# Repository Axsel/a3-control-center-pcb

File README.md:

# A3 Control Center PCB

Revision A design for a USB-powered ESP32-WROOM-32E-N4 controller with independent
high-speed and fault-tolerant CAN buses, a replaceable SSD1306 OLED, and an
analog composite-video output.

## Status

Phase 1 architecture was approved on 2026-10-02. The Phase 2 schematic and
100 x 70 mm four-layer PCB are electrically complete for USB/power, ESP32/UI,
CAN_HS, CAN_FT, and composite video. A deterministic 19-stage layout rebuild
under KiCad 10.0.6 now reports **ERC 0, DRC 0, and 0 unconnected items**. A local
pre-release manufacturing audit package exists under
`manufacturing/generated/rev-a-audit/`, but no order-ready manufacturing release
has been created. LCSC identities are qualified for all 97 candidate
references; high-voltage C1 now uses PSA FV32N472J102EFG / C5156737 from JLC
global sourcing. The U5, U10, J1, and J60 critical footprints have passed
independent dimensional audits; JLC confirmation of the RCA plated slot, USB
connector assembly handling, physical connector fit checks, stock reservation,
and purchasing/source resolution remain release gates. The three-button part
identity is resolved by an audited same-footprint change to
TL3301NF260QG/C273528; the current consolidated JLC workbook allocates all six
needed switches. The former CP2102N stock gate is closed by using
Silicon Labs' electrically identical tape-and-reel order code
CP2102N-A02-GQFN28R/C964632. The project owner has
accepted deferring composite-video electrical and JVC compatibility validation
until assembled Revision A boards arrive; those tests remain mandatory during
bring-up but are no longer a prototype-order blocker.
The manufacturing contract requires JLCPCB to fit every board connector:
J1/J10/J20/J40/J60 are present in both the candidate BOM and full CPL for
manual/wave assembly; the user is not expected to solder connectors.
An independent layer-by-layer Gerber/drill render review is also complete, with
its evidence and limitations recorded in `docs/rev-a-fabrication-review.md`.

For quick repository browsing, see the
[Revision A rendered views](docs/revision-a-rendered-views.md), including the
complete schematic PDF, per-sheet previews, PCB top/bottom renders, assembly
drawing, and fabrication-layer images.

The originally requested ESP32-WROOM-32 was replaced with the manufacturer-
recommended `ESP32-WROOM-32E-N4` after project-owner authorization. The change
preserves the classic ESP32 architecture, 4 MB flash, PCB antenna, DAC1/DAC2,
TWAI, firmware pin map, and module envelope while avoiding an NRND part. The
manufacturer land pattern and antenna keepout for the 32E are mandatory.

## Repository map

- `docs/`: architecture, interfaces, calculations, decisions, and test plans
- `hardware/`: KiCad 10 project, design rules, and project-local libraries
- `datasheets/`: source index; vendor PDFs are not copied into Git by default
- `bom/`: controlled, provisional BOM
- `firmware/`: synchronized GPIO contract and video feasibility notes
- `scripts/`: KiCad CLI wrapper plus validation/export automation
- `manufacturing/`: controlled release area plus the tracked Revision A audit
  snapshot used by the rendered-view index

The remaining JLC engineering and global-sourcing questions are consolidated
in `manufacturing/jlcpcb-support-request.md` for submission before payment.

## Tooling note

The container now has KiCad 10.0.6 and its matching official symbols,
footprints, templates, and 3D models. Use `./scripts/kicad-cli`; headless ERC and
DRC were validated against an installed reference project. Installation details
and the remaining Phase 2 inputs are recorded in `docs/toolchain.md`.

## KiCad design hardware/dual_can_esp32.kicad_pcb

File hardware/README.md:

# Hardware workspace

Phase 2 contains a native KiCad 10.0.6 project, a complete hierarchical
schematic, a four-layer 100 x 70 mm PCB with all 130 electrical footprints plus
four board-only M3 mounting holes functionally placed, JLCPCB-oriented custom
design rules, and project-local library tables. USB data, both converter local
power stages, protected USB 5 V and 5V_FT distribution, and the MCP2515 crystal
nets are routed over a filled continuous L2 ground plane. The rest of the board
is intentionally still in routing development; this is not a manufacturing
release.

Project-local symbol and footprint libraries contain the Kycon KLPX RCA and
TPS63070 RNM0015A land patterns. The DFR0486 OLED is cable mounted through an
official-library JST-PH footprint; any device whose installed-library
pin/package mapping cannot be proven from its datasheet remains a local-library
candidate. The KiCad 10 official USB4105 footprint is present and matches the
selected GCT family. Its signal/contact orientation and edge-mounted
shell-stake clearances have been checked in the current placement; a final
drawing/Gerber overlay is still required before release.

The MCU is `ESP32-WROOM-32E-N4`. Its KiCad footprint has been checked for the 38
castellated pads, thermal ground land/vias, module outline, and antenna keepout
against Figure 13 of Espressif datasheet v2.1. The antenna is placed at the top
board edge; the keepout must be rechecked in final Gerbers after zones exist.

J20/J40 use Phoenix Contact item 1715734 (`MKDS 1,5/ 3-5,08`) and the audited
KiCad 10 official 5.08 mm MKDS footprint. This is the three-independent-potential
part; the similarly named internally commoned `-B-` variant is not acceptable.

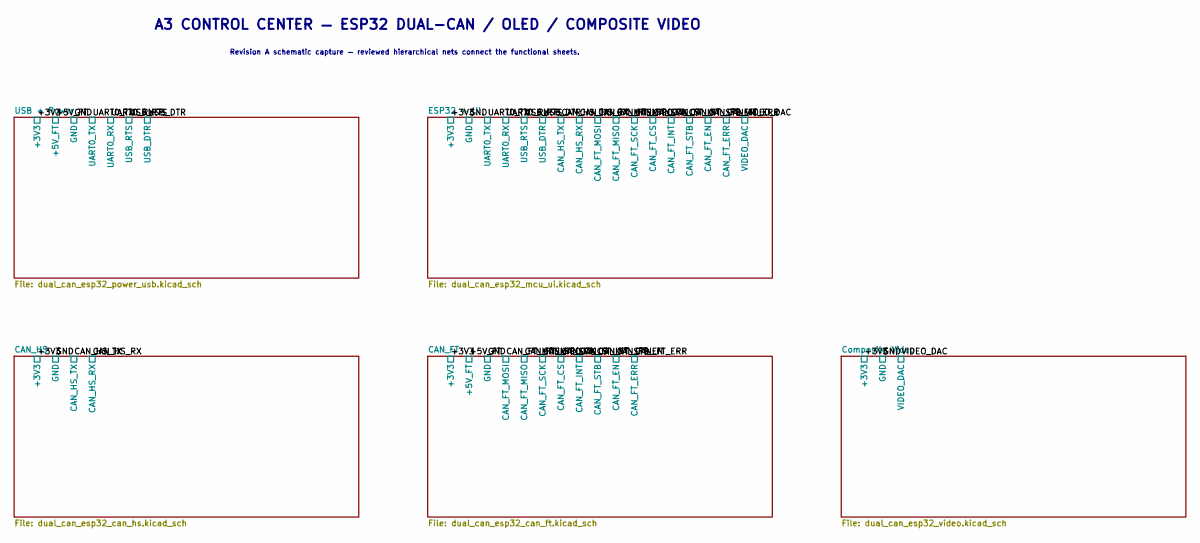
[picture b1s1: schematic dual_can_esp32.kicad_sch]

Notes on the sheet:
Revision A schematic capture — reviewed hierarchical nets connect the functional sheets.
A3 CONTROL CENTER — ESP32 DUAL-CAN / OLED / COMPOSITE VIDEO

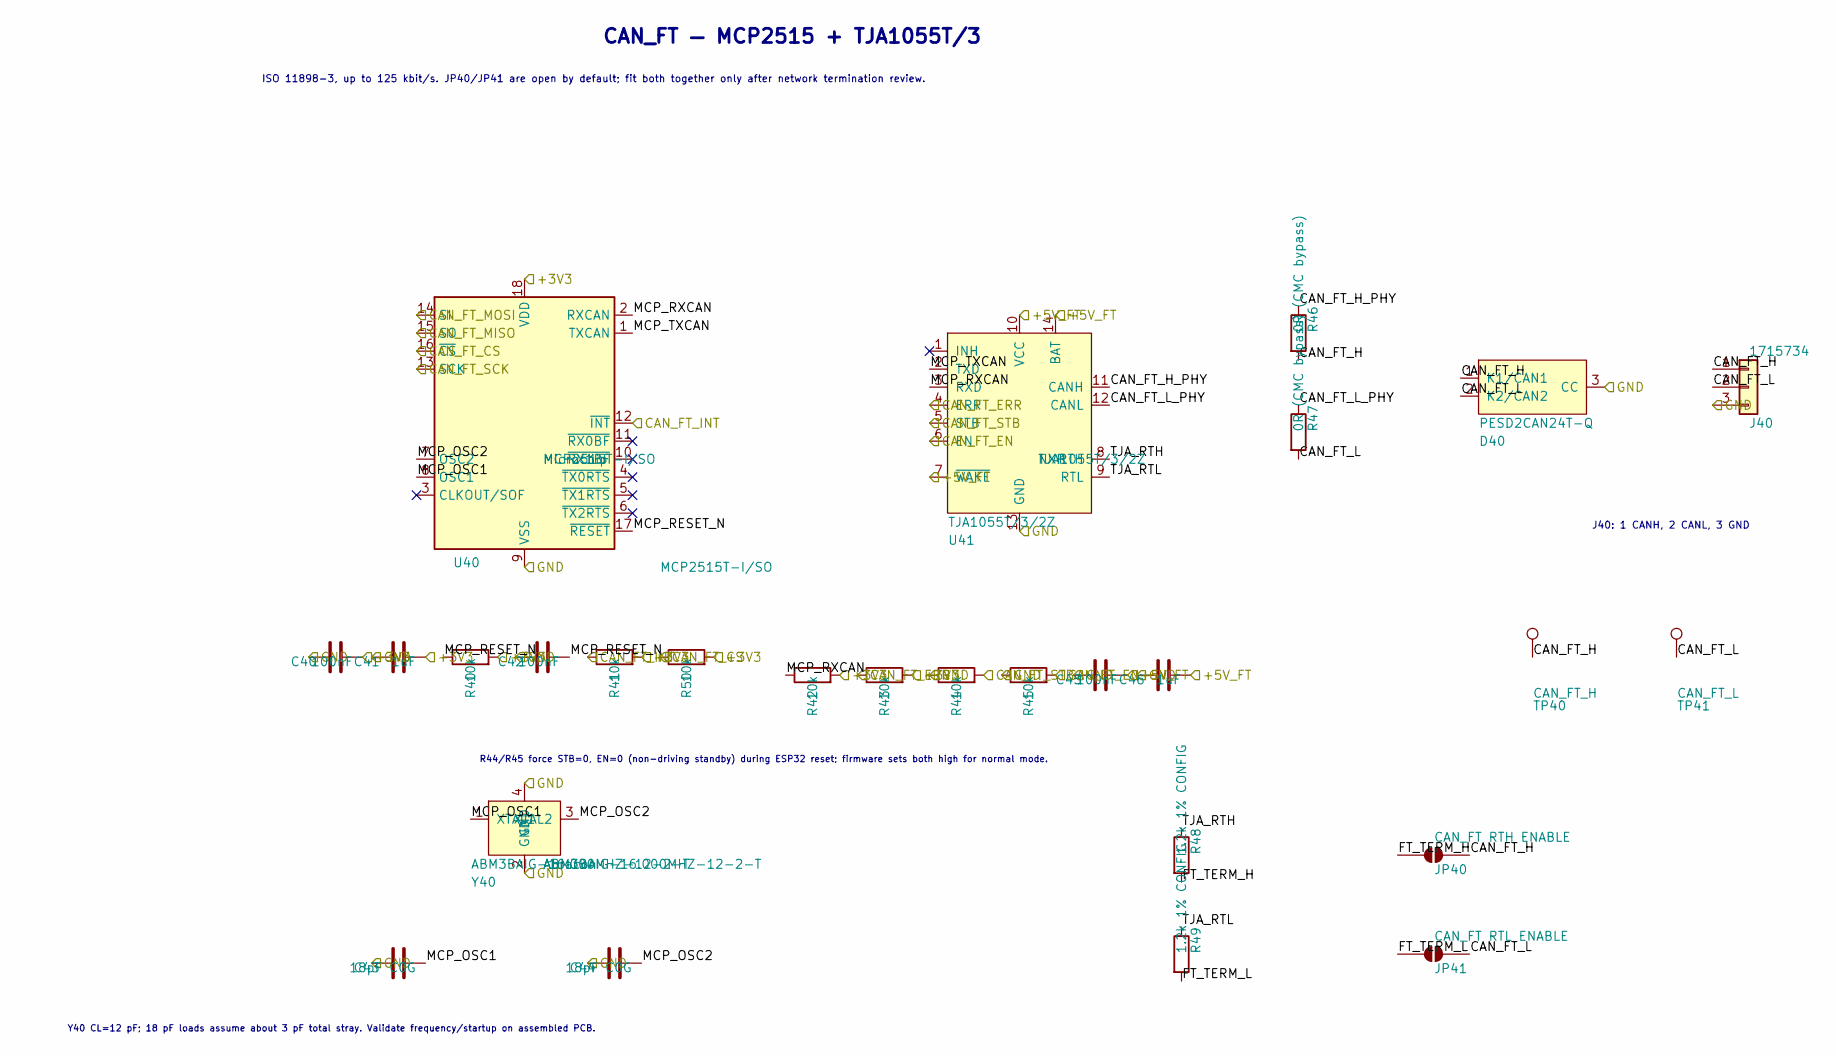
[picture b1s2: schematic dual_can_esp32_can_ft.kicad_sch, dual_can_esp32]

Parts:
C40, C42, C45: 100nF; C_0603_1608Metric
C41, C46: 1uF; C_0805_2012Metric
C43, C44: 18pF C0G; C_0603_1608Metric
D40: PESD2CAN24T-Q; SOT-23
J40: 1715734; TerminalBlock_Phoenix_MKDS-1,5-3-5.08_1x03_P5.08mm_Horizont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
JP40: CAN_FT RTH ENABLE; SolderJumper-2_P1.3mm_Open_RoundedPad1.0x1.5mm
JP41: CAN_FT RTL ENABLE; SolderJumper-2_P1.3mm_Open_RoundedPad1.0x1.5mm
R40, R41, R42, R43, R44, R45, R50: 10k; R_0603_1608Metric
R46, R47: 0R (CMC bypass); R_0603_1608Metric
R48, R49: 1.2k 1% CONFIG; R_0603_1608Metric
TP40: CAN_FT_H; TestPoint_Pad_D1.0mm
TP41: CAN_FT_L; TestPoint_Pad_D1.0mm
U40: MCP2515T-I/SO; SOIC-18W_7.5x11.6mm_P1.27mm; MPN MCP2515T-I/SO
U41: TJA1055T/3/2Z; SO-14_3.9x8.65mm_P1.27mm; MPN TJA1055T/3/2Z
Y40: ABM3BAIG-16.000MHZ-12-2-T; Crystal_SMD_5032-4Pin_5.0x3.2mm; MPN ABM3BAIG-16.000MHZ-12-2-T

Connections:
/+3V3: C40.2, C41.2, R40.2, R41.2, R42.2, R43.2, R50.2, U40.18 (VDD); also elsewhere on the board
/+5V_FT: C45.2, C46.2, U41.7 (~WAKE), U41.10 (VCC), U41.14 (BAT); also elsewhere on the board
/CAN_FT/CAN_FT_H: D40.1 (K1/CAN1), J40.1, JP40.2 (B), R46.2, TP40.1 (1_1)
/CAN_FT/CAN_FT_H_PHY: R46.1, U41.11 (CANH)
/CAN_FT/CAN_FT_L: D40.2 (K2/CAN2), J40.2, JP41.2 (B), R47.2, TP41.1 (1_1)
/CAN_FT/CAN_FT_L_PHY: R47.1, U41.12 (CANL)
/CAN_FT/FT_TERM_H: JP40.1 (A), R48.2
/CAN_FT/FT_TERM_L: JP41.1 (A), R49.2
/CAN_FT/MCP_OSC1: C43.2, U40.8 (OSC1), Y40.1 (XTAL1)
/CAN_FT/MCP_OSC2: C44.2, U40.7 (OSC2), Y40.3 (XTAL2)
/CAN_FT/MCP_RESET_N: C42.2, R40.1, U40.17 (~RESET)
/CAN_FT/MCP_RXCAN: R42.1, U40.2 (RXCAN), U41.3 (RXD)
/CAN_FT/MCP_TXCAN: U40.1 (TXCAN), U41.2 (TXD)
/CAN_FT/TJA_RTH: R48.1, U41.8 (RTH)
/CAN_FT/TJA_RTL: R49.1, U41.9 (RTL)
/CAN_FT_CS: R50.1, U40.16 (~CS); also elsewhere on the board
/CAN_FT_EN: R45.2, U41.6 (EN); also elsewhere on the board
/CAN_FT_ERR: R43.1, U41.4 (ERR); also elsewhere on the board
/CAN_FT_INT: R41.1, U40.12 (~INT); also elsewhere on the board
/CAN_FT_MISO: U40.15 (SO); also elsewhere on the board
/CAN_FT_MOSI: U40.14 (SI); also elsewhere on the board
/CAN_FT_SCK: U40.13 (SCK); also elsewhere on the board
/CAN_FT_STB: R44.2, U41.5 (STB); also elsewhere on the board
/GND: C40.1, C41.1, C42.1, C43.1, C44.1, C45.1, C46.1, D40.3 (CC), J40.3, R44.1, R45.1, U40.9 (VSS), U41.13 (GND), Y40.2 (GND), Y40.4 (GND); also elsewhere on the board

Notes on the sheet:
R44/R45 force STB=0, EN=0 (non-driving standby) during ESP32 reset; firmware sets both high for normal mode.
J40: 1 CANH, 2 CANL, 3 GND
Y40 CL=12 pF; 18 pF loads assume about 3 pF total stray. Validate frequency/startup on assembled PCB.
CAN_FT — MCP2515 + TJA1055T/3
ISO 11898-3, up to 125 kbit/s. JP40/JP41 are open by default; fit both together only after network termination review.

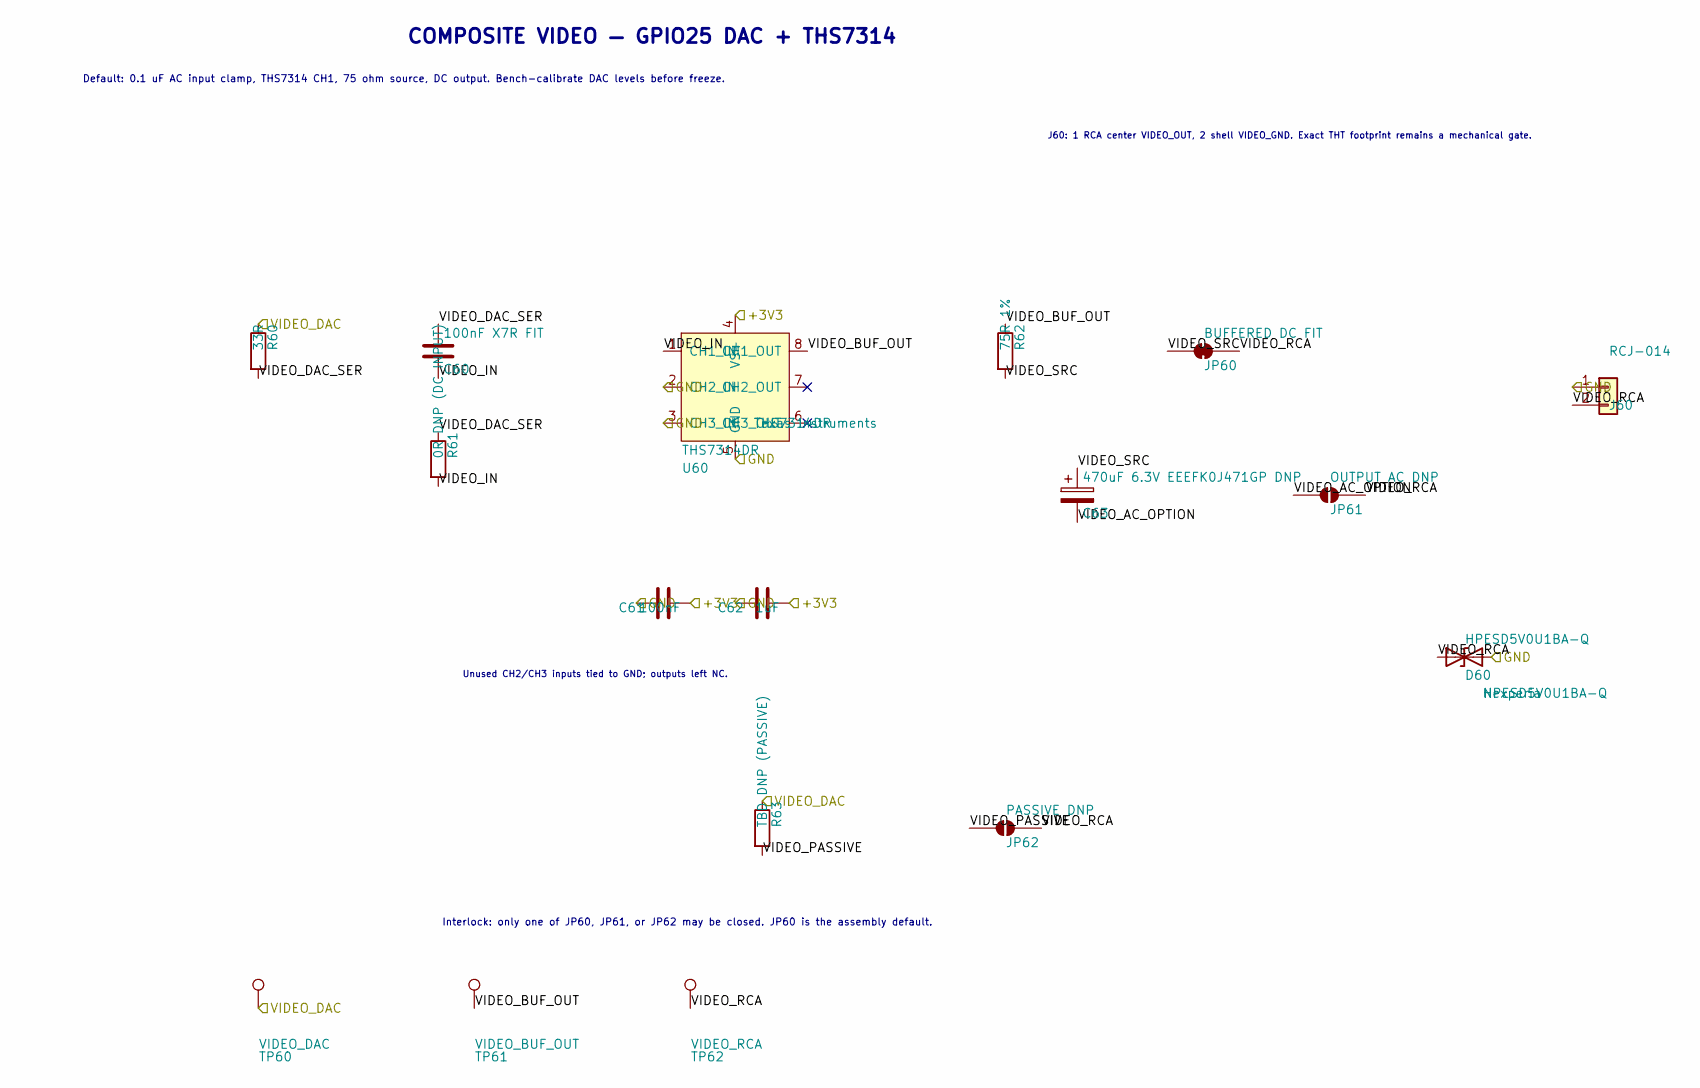
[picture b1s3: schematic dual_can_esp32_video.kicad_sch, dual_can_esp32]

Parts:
C60: 100nF X7R FIT; C_0805_2012Metric
C61: 100nF; C_0603_1608Metric
C62: 1uF; C_0805_2012Metric
C63: 470uF 6.3V EEEFK0J471GP DNP; CP_Elec_8x10
D60: HPESD5V0U1BA-Q; D_SOD-323; MPN HPESD5V0U1BA-Q
J60: RCJ-014
JP60: BUFFERED DC FIT; SolderJumper-2_P1.3mm_Bridged_RoundedPad1.0x1.5mm
JP61: OUTPUT AC DNP; SolderJumper-2_P1.3mm_Open_RoundedPad1.0x1.5mm
JP62: PASSIVE DNP; SolderJumper-2_P1.3mm_Open_RoundedPad1.0x1.5mm
R60: 33R; R_0603_1608Metric
R61: 0R DNP (DC INPUT); R_0603_1608Metric
R62: 75R 1%; R_0603_1608Metric
R63: TBD DNP (PASSIVE); R_0603_1608Metric
TP60: VIDEO_DAC; TestPoint_Pad_D1.0mm
TP61: VIDEO_BUF_OUT; TestPoint_Pad_D1.0mm
TP62: VIDEO_RCA; TestPoint_Pad_D1.0mm
U60: THS7314DR; SOIC-8_3.9x4.9mm_P1.27mm; MPN THS7314DR

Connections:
/+3V3: C61.2, C62.2, U60.4 (VS+); also elsewhere on the board
/Composite Video/VIDEO_AC_OPTION: C63.2, JP61.1 (A)
/Composite Video/VIDEO_BUF_OUT: R62.1, TP61.1 (1_1), U60.8 (CH1_OUT)
/Composite Video/VIDEO_DAC_SER: C60.1, R60.2, R61.1
/Composite Video/VIDEO_IN: C60.2, R61.2, U60.1 (CH1_IN)
/Composite Video/VIDEO_PASSIVE: JP62.1 (A), R63.2
/Composite Video/VIDEO_RCA: D60.1 (A1), J60.2, JP60.2 (B), JP61.2 (B), JP62.2 (B), TP62.1 (1_1)
/Composite Video/VIDEO_SRC: C63.1, JP60.1 (A), R62.2
/GND: C61.1, C62.1, D60.2 (A2), J60.1, U60.2 (CH2_IN), U60.3 (CH3_IN), U60.5 (GND); also elsewhere on the board
/VIDEO_DAC: R60.1, R63.1, TP60.1 (1_1); also elsewhere on the board

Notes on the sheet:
Default: 0.1 uF AC input clamp, THS7314 CH1, 75 ohm source, DC output. Bench-calibrate DAC levels before freeze.
J60: 1 RCA center VIDEO_OUT, 2 shell VIDEO_GND. Exact THT footprint remains a mechanical gate.
Interlock: only one of JP60, JP61, or JP62 may be closed. JP60 is the assembly default.
Unused CH2/CH3 inputs tied to GND; outputs left NC.
COMPOSITE VIDEO — GPIO25 DAC + THS7314

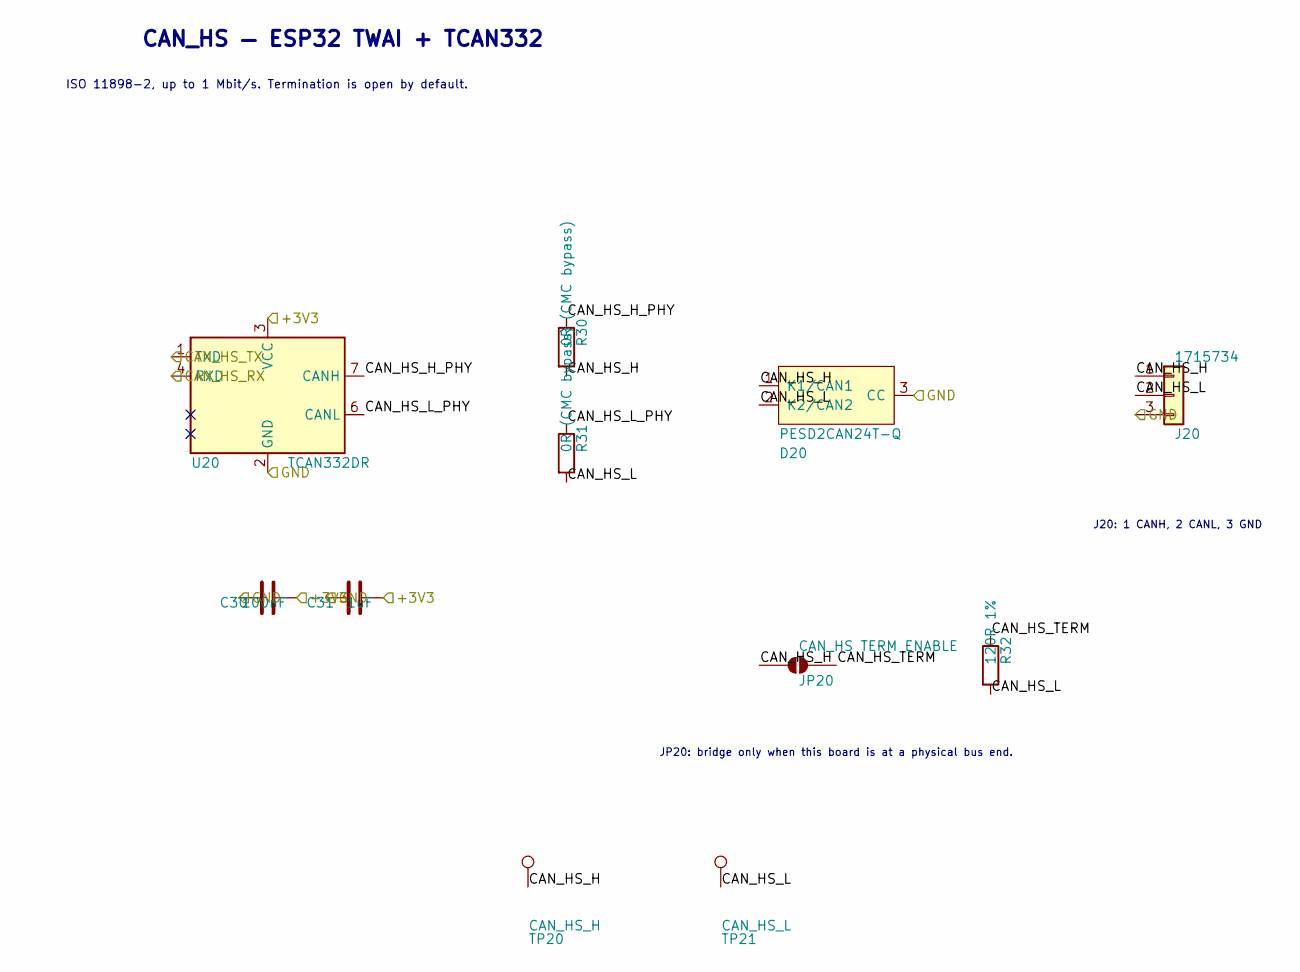
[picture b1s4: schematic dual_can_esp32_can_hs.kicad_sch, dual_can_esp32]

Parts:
C30: 100nF; C_0603_1608Metric
C31: 1uF; C_0805_2012Metric
D20: PESD2CAN24T-Q; SOT-23
J20: 1715734; TerminalBlock_Phoenix_MKDS-1,5-3-5.08_1x03_P5.08mm_Horizont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
JP20: CAN_HS TERM ENABLE; SolderJumper-2_P1.3mm_Open_RoundedPad1.0x1.5mm
R30, R31: 0R (CMC bypass); R_0603_1608Metric
R32: 120R 1%; R_0603_1608Metric
TP20: CAN_HS_H; TestPoint_Pad_D1.0mm
TP21: CAN_HS_L; TestPoint_Pad_D1.0mm
U20: TCAN332DR; SOIC-8_3.9x4.9mm_P1.27mm

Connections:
/+3V3: C30.2, C31.2, U20.3 (VCC); also elsewhere on the board
/CAN_HS/CAN_HS_H: D20.1 (K1/CAN1), J20.1, JP20.1 (A), R30.2, TP20.1 (1_1)
/CAN_HS/CAN_HS_H_PHY: R30.1, U20.7 (CANH)
/CAN_HS/CAN_HS_L: D20.2 (K2/CAN2), J20.2, R31.2, R32.2, TP21.1 (1_1)
/CAN_HS/CAN_HS_L_PHY: R31.1, U20.6 (CANL)
/CAN_HS/CAN_HS_TERM: JP20.2 (B), R32.1
/CAN_HS_RX: U20.4 (RXD); also elsewhere on the board
/CAN_HS_TX: U20.1 (TXD); also elsewhere on the board
/GND: C30.1, C31.1, D20.3 (CC), J20.3, U20.2 (GND); also elsewhere on the board

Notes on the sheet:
CAN_HS — ESP32 TWAI + TCAN332
J20: 1 CANH, 2 CANL, 3 GND
ISO 11898-2, up to 1 Mbit/s. Termination is open by default.
JP20: bridge only when this board is at a physical bus end.

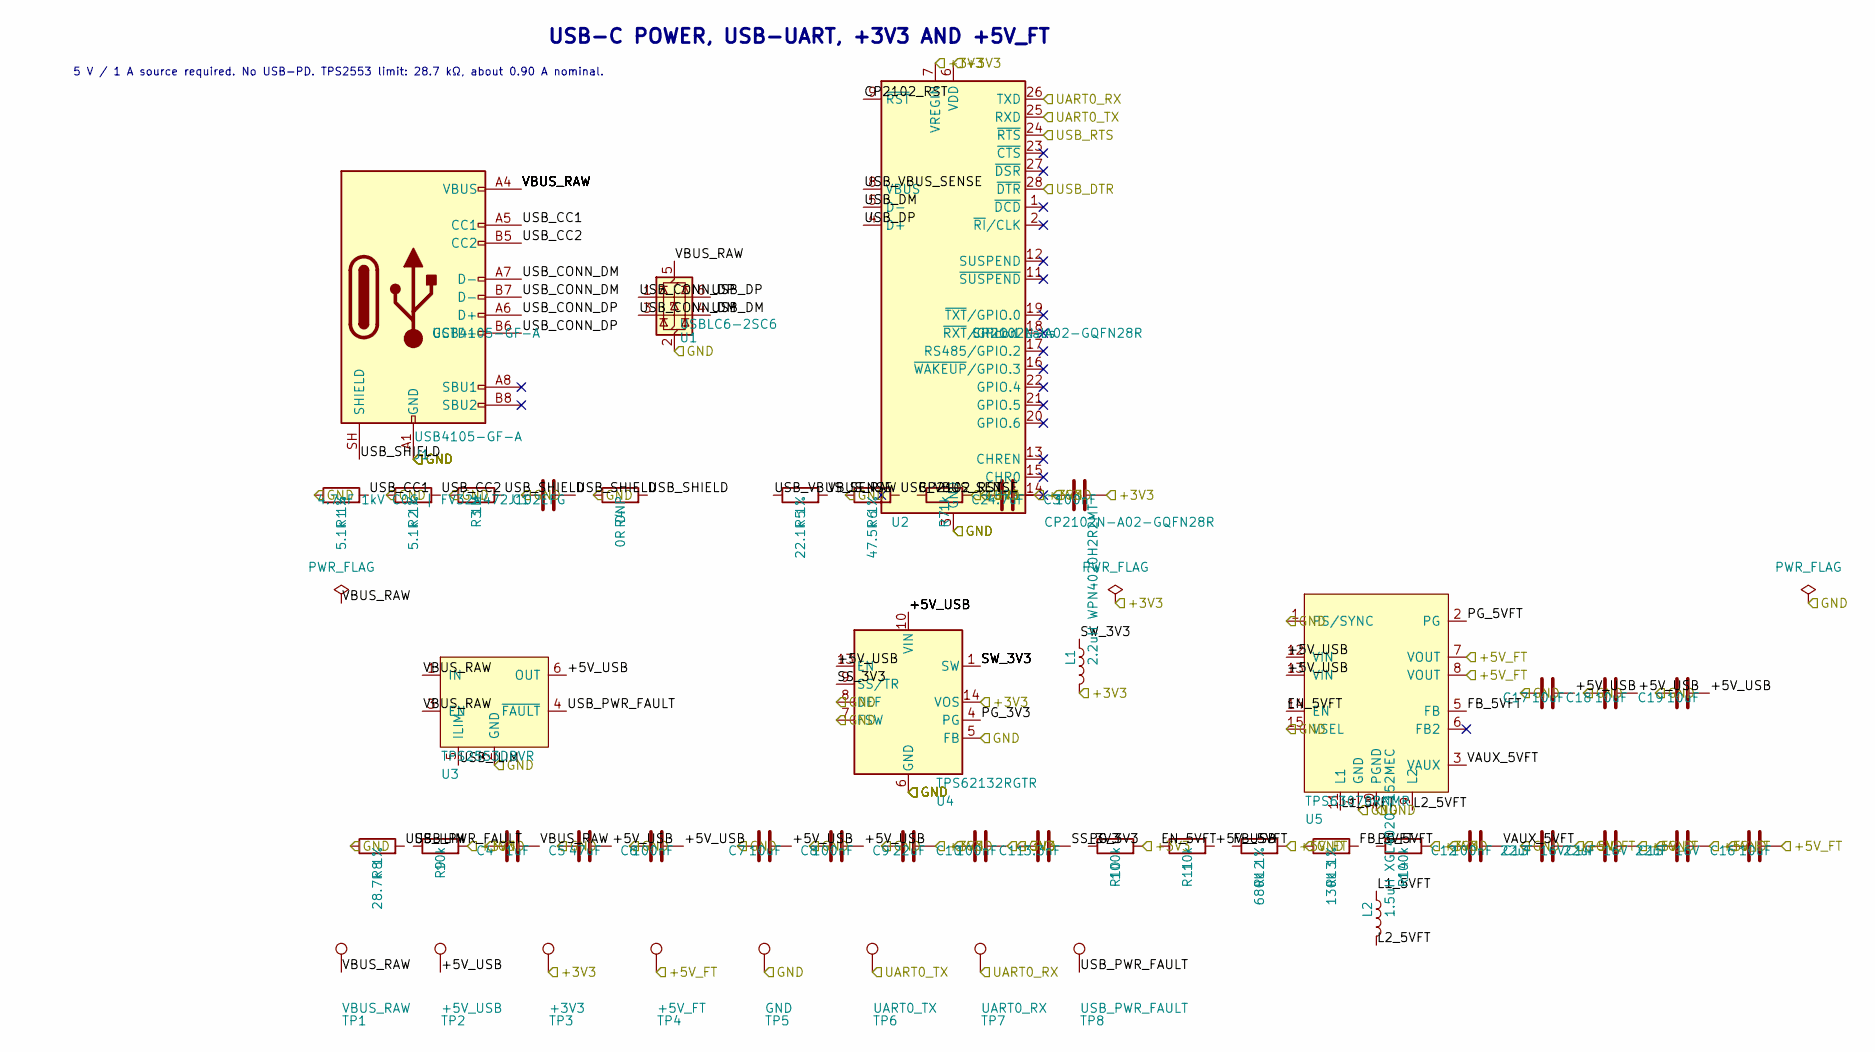
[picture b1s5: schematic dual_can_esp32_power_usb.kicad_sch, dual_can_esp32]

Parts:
C1: 4.7nF 1kV C0G | FV32N472J102EFG; C_1210_3225Metric
C2: 4.7uF; C_0805_2012Metric
C3, C6, C8, C10, C12: 100nF; C_0603_1608Metric
C4: 1uF; C_0805_2012Metric
C5: 47uF; C_1210_3225Metric
C7, C17, C18: 10uF; C_0805_2012Metric
C9: 22uF; C_0805_2012Metric
C11: 3.3nF; C_0603_1608Metric
C13, C14, C15: 22uF 16V; C_0805_2012Metric
C16, C19: 10uF; C_0603_1608Metric
J1: USB4105-GF-A; USB_C_Receptacle_GCT_USB4105-xx-A_16P_TopMnt_Horizontal; MPN USB4105-GF-A
L1: 2.2uH WPN4020H2R2MT; WPN4020H
L2: 1.5uH XGL4020-152MEC; L_Coilcraft_XxL4020
R1, R2: 5.1k 1%; R_0603_1608Metric
R3: 1M; R_0603_1608Metric
R4: 0R DNP; R_0603_1608Metric
R5: 22.1k 1%; R_0603_1608Metric
R6: 47.5k 1%; R_0603_1608Metric
R7: 1k; R_0603_1608Metric
R8: 28.7k 1%; R_0603_1608Metric
R9, R11: 10k; R_0603_1608Metric
R10, R14: 100k; R_0603_1608Metric
R12: 680k 1%; R_0603_1608Metric
R13: 130k 1%; R_0603_1608Metric
TP1: VBUS_RAW; TestPoint_Pad_D1.0mm
TP2: +5V_USB; TestPoint_Pad_D1.0mm
TP3: +3V3; TestPoint_Pad_D1.0mm
TP4: +5V_FT; TestPoint_Pad_D1.0mm
TP5: GND; TestPoint_Pad_D1.0mm
TP6: UART0_TX; TestPoint_Pad_D1.0mm
TP7: UART0_RX; TestPoint_Pad_D1.0mm
TP8: USB_PWR_FAULT; TestPoint_Pad_D1.0mm
U1: USBLC6-2SC6; SOT-23-6
U2: CP2102N-A02-GQFN28R; QFN-28-1EP_5x5mm_P0.5mm_EP3.35x3.35mm; MPN CP2102N-A02-GQFN28R
U3: TPS2553DBVR; SOT-23-6
U4: TPS62132RGTR; VQFN-16-1EP_3x3mm_P0.5mm_EP1.68x1.68mm_ThermalVias
U5: TPS63070RNMR; TI_RNM0015A_VQFN-HR-15

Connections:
/+3V3: C2.2, C3.2, C9.2, C10.2, L1.2, R7.2, R9.2, R10.2, R14.2, TP3.1 (1_1), U2.6 (VDD), U2.7 (VREGIN), U4.14 (VOS); also elsewhere on the board
/+5V_FT: C13.2, C14.2, C15.2, C16.2, R12.2, TP4.1 (1_1), U5.7 (VOUT), U5.8 (VOUT); also elsewhere on the board
/GND: C1.1, C2.1, C3.1, C4.1, C5.1, C6.1, C7.1, C8.1, C9.1, C10.1, C11.1, C12.1, C13.1, C14.1, C15.1, C16.1, C17.1, C18.1, C19.1, J1.A1 (GND), J1.A12 (GND), J1.B1 (GND), J1.B12 (GND), R1.1, R2.1, R3.1, R4.1, R6.1, R8.1, R13.1, TP5.1 (1_1), U1.2 (GND), U2.3 (GND), U2.29 (GND), U3.2 (GND), U4.5 (FB), U4.6 (GND), U4.7 (FSW), U4.8 (DEF), U4.15 (GND), U4.16 (GND), U4.17 (GND), U5.1 (PS/SYNC), U5.4 (GND), U5.10 (PGND), U5.15 (VSEL); also elsewhere on the board
/UART0_RX: TP7.1 (1_1), U2.26 (TXD); also elsewhere on the board
/UART0_TX: TP6.1 (1_1), U2.25 (RXD); also elsewhere on the board
/USB + Power/+5V_USB: C5.2, C6.2, C7.2, C8.2, C17.2, C18.2, C19.2, R11.2, TP2.1 (1_1), U3.6 (OUT), U4.10 (VIN), U4.11 (VIN), U4.12 (VIN), U4.13 (EN), U5.12 (VIN), U5.13 (VIN)
/USB + Power/CP2102_RST: R7.1, U2.9 (~RST)
/USB + Power/EN_5VFT: R11.1, U5.14 (EN)
/USB + Power/FB_5VFT: R12.1, R13.2, U5.5 (FB)
/USB + Power/L1_5VFT: L2.1, U5.11 (L1)
/USB + Power/L2_5VFT: L2.2, U5.9 (L2)
/USB + Power/PG_3V3: R10.1, U4.4 (PG)
/USB + Power/PG_5VFT: R14.1, U5.2 (PG)
/USB + Power/SS_3V3: C11.2, U4.9 (SS/TR)
/USB + Power/SW_3V3: L1.1, U4.1 (SW), U4.2 (SW), U4.3 (SW)
/USB + Power/USB_CC1: J1.A5 (CC1), R1.2
/USB + Power/USB_CC2: J1.B5 (CC2), R2.2
/USB + Power/USB_CONN_DM: J1.A7 (D-), J1.B7 (D-), U1.3 (I/O2)
/USB + Power/USB_CONN_DP: J1.A6 (D+), J1.B6 (D+), U1.1 (I/O1)
/USB + Power/USB_DM: U1.4 (I/O2), U2.5 (D-)
/USB + Power/USB_DP: U1.6 (I/O1), U2.4 (D+)
/USB + Power/USB_ILIM: R8.2, U3.5 (ILIM)
/USB + Power/USB_PWR_FAULT: R9.1, TP8.1 (1_1), U3.4 (~FAULT)
/USB + Power/USB_SHIELD: C1.2, J1.SH (SHIELD), R3.2, R4.2
/USB + Power/USB_VBUS_SENSE: R5.1, R6.2, U2.8 (VBUS)
/USB + Power/VAUX_5VFT: C12.2, U5.3 (VAUX)
/USB + Power/VBUS_RAW: C4.2, J1.A4 (VBUS), J1.A9 (VBUS), J1.B4 (VBUS), J1.B9 (VBUS), R5.2, TP1.1 (1_1), U1.5 (VBUS), U3.1 (IN), U3.3 (EN)
/USB_DTR: U2.28 (~DTR); also elsewhere on the board
/USB_RTS: U2.24 (~RTS); also elsewhere on the board

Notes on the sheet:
5 V / 1 A source required. No USB-PD. TPS2553 limit: 28.7 kΩ, about 0.90 A nominal.
USB-C POWER, USB-UART, +3V3 AND +5V_FT

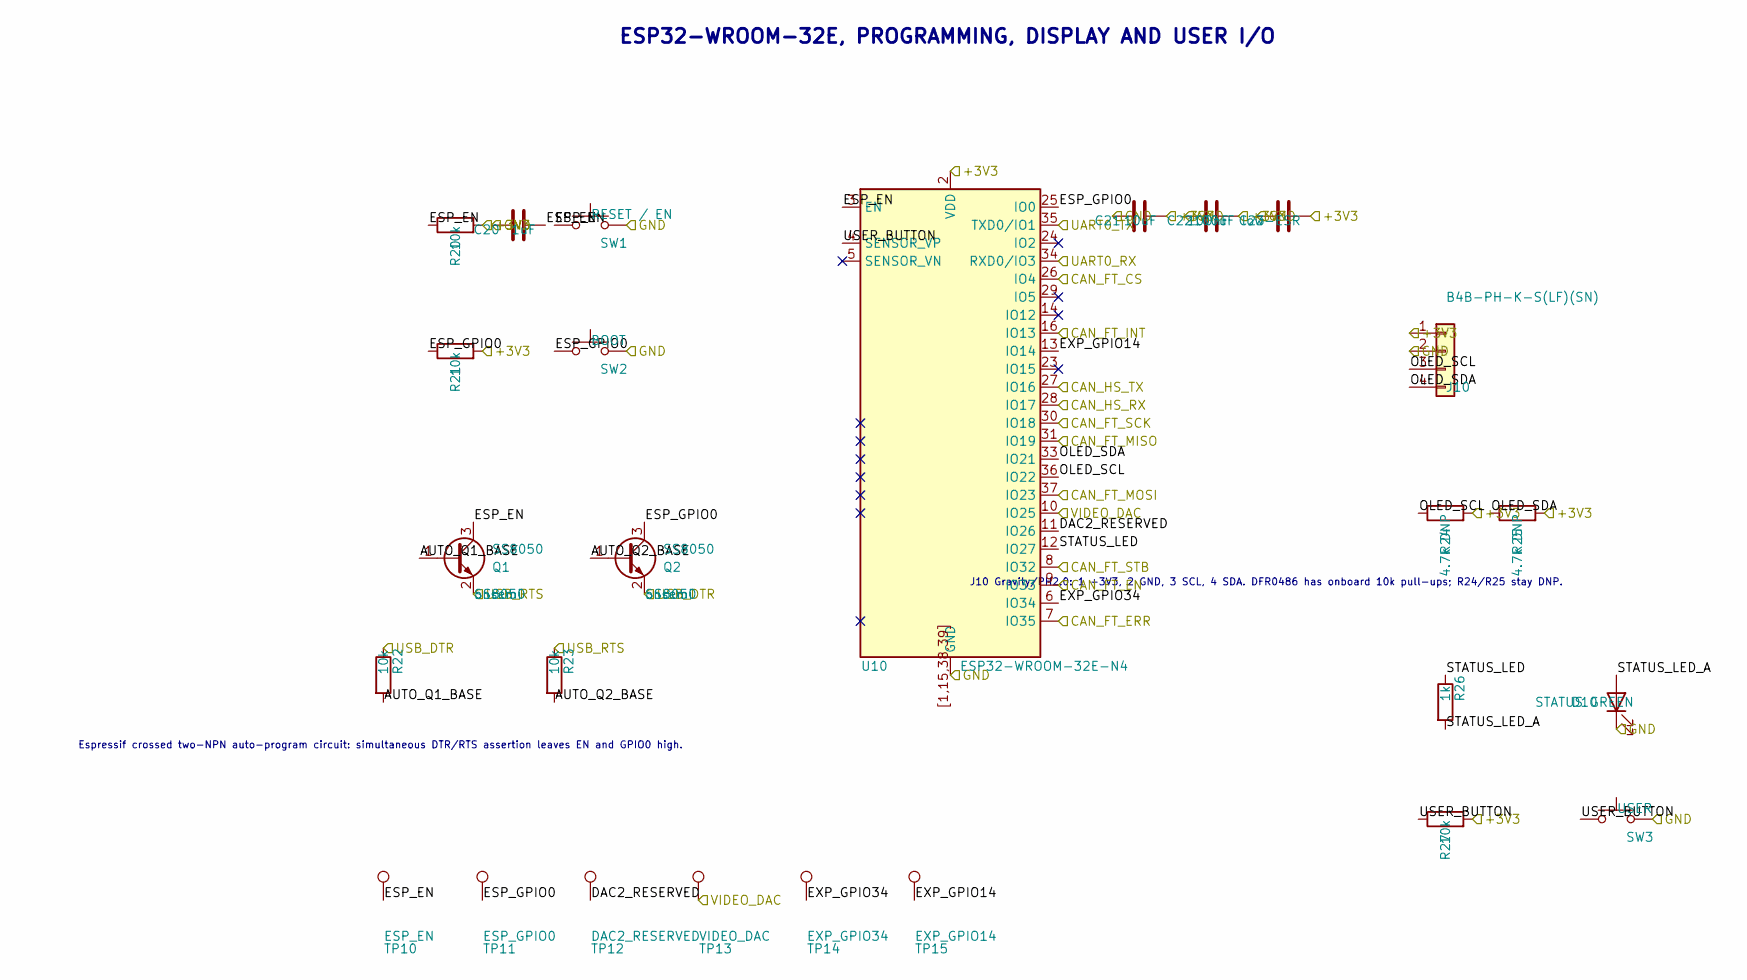
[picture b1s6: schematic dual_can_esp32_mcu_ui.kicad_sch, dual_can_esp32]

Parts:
C20: 1uF; C_0805_2012Metric
C21: 10uF; C_0805_2012Metric
C22: 100nF; C_0603_1608Metric
C23: 100uF low-ESR; C_1210_3225Metric
D10: STATUS GREEN; LED_0603_1608Metric
J10: B4B-PH-K-S(LF)(SN); JST_PH_B4B-PH-K_1x04_P2.00mm_Vertical
Q1, Q2: SS8050; SOT-23; MPN SS8050
R20, R21, R22, R23, R27: 10k; R_0603_1608Metric
R24, R25: 4.7k DNP; R_0603_1608Metric
R26: 1k; R_0603_1608Metric
SW1: RESET / EN; SW_Push_1P1T_NO_E-Switch_TL3301NxxxxxG
SW2: BOOT; SW_Push_1P1T_NO_E-Switch_TL3301NxxxxxG
SW3: USER; SW_Push_1P1T_NO_E-Switch_TL3301NxxxxxG
TP10: ESP_EN; TestPoint_Pad_D1.0mm
TP11: ESP_GPIO0; TestPoint_Pad_D1.0mm
TP12: DAC2_RESERVED; TestPoint_Pad_D1.0mm
TP13: VIDEO_DAC; TestPoint_Pad_D1.0mm
TP14: EXP_GPIO34; TestPoint_Pad_D1.0mm
TP15: EXP_GPIO14; TestPoint_Pad_D1.0mm
U10: ESP32-WROOM-32E-N4; ESP32-WROOM-32E

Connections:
/+3V3: C21.2, C22.2, C23.2, J10.1, R20.2, R21.2, R24.2, R25.2, R27.2, U10.2 (VDD); also elsewhere on the board
/CAN_FT_CS: U10.26 (IO4); also elsewhere on the board
/CAN_FT_EN: U10.9 (IO33); also elsewhere on the board
/CAN_FT_ERR: U10.7 (IO35); also elsewhere on the board
/CAN_FT_INT: U10.16 (IO13); also elsewhere on the board
/CAN_FT_MISO: U10.31 (IO19); also elsewhere on the board
/CAN_FT_MOSI: U10.37 (IO23); also elsewhere on the board
/CAN_FT_SCK: U10.30 (IO18); also elsewhere on the board
/CAN_FT_STB: U10.8 (IO32); also elsewhere on the board
/CAN_HS_RX: U10.28 (IO17); also elsewhere on the board
/CAN_HS_TX: U10.27 (IO16); also elsewhere on the board
/ESP32 + UI/AUTO_Q1_BASE: Q1.1 (B), R22.2
/ESP32 + UI/AUTO_Q2_BASE: Q2.1 (B), R23.2
/ESP32 + UI/DAC2_RESERVED: TP12.1 (1_1), U10.11 (IO26)
/ESP32 + UI/ESP_EN: C20.2, Q1.3 (C), R20.1, SW1.1, TP10.1 (1_1), U10.3 (EN)
/ESP32 + UI/ESP_GPIO0: Q2.3 (C), R21.1, SW2.1, TP11.1 (1_1), U10.25 (IO0)
/ESP32 + UI/EXP_GPIO14: TP15.1 (1_1), U10.13 (IO14)
/ESP32 + UI/EXP_GPIO34: TP14.1 (1_1), U10.6 (IO34)
/ESP32 + UI/OLED_SCL: J10.3, R24.1, U10.36 (IO22)
/ESP32 + UI/OLED_SDA: J10.4, R25.1, U10.33 (IO21)
/ESP32 + UI/STATUS_LED: R26.1, U10.12 (IO27)
/ESP32 + UI/STATUS_LED_A: D10.2 (A), R26.2
/ESP32 + UI/USER_BUTTON: R27.1, SW3.1, U10.4 (SENSOR_VP)
/GND: C20.1, C21.1, C22.1, C23.1, D10.1 (K), J10.2, SW1.2, SW2.2, SW3.2, U10.1 (GND), U10.15 (GND), U10.38 (GND), U10.39 (GND), U10.[1,15,38,39] (GND); also elsewhere on the board
/UART0_RX: U10.34 (RXD0/IO3); also elsewhere on the board
/UART0_TX: U10.35 (TXD0/IO1); also elsewhere on the board
/USB_DTR: Q2.2 (E), R22.1; also elsewhere on the board
/USB_RTS: Q1.2 (E), R23.1; also elsewhere on the board
/VIDEO_DAC: TP13.1 (1_1), U10.10 (IO25); also elsewhere on the board

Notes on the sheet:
Espressif crossed two-NPN auto-program circuit: simultaneous DTR/RTS assertion leaves EN and GPIO0 high.
J10 Gravity/PH2.0: 1 +3V3, 2 GND, 3 SCL, 4 SDA. DFR0486 has onboard 10k pull-ups; R24/R25 stay DNP.
ESP32-WROOM-32E, PROGRAMMING, DISPLAY AND USER I/O
